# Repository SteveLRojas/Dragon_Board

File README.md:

# Dragon_Board
Custom FPGA board designed for TRS-80 and NES projects.

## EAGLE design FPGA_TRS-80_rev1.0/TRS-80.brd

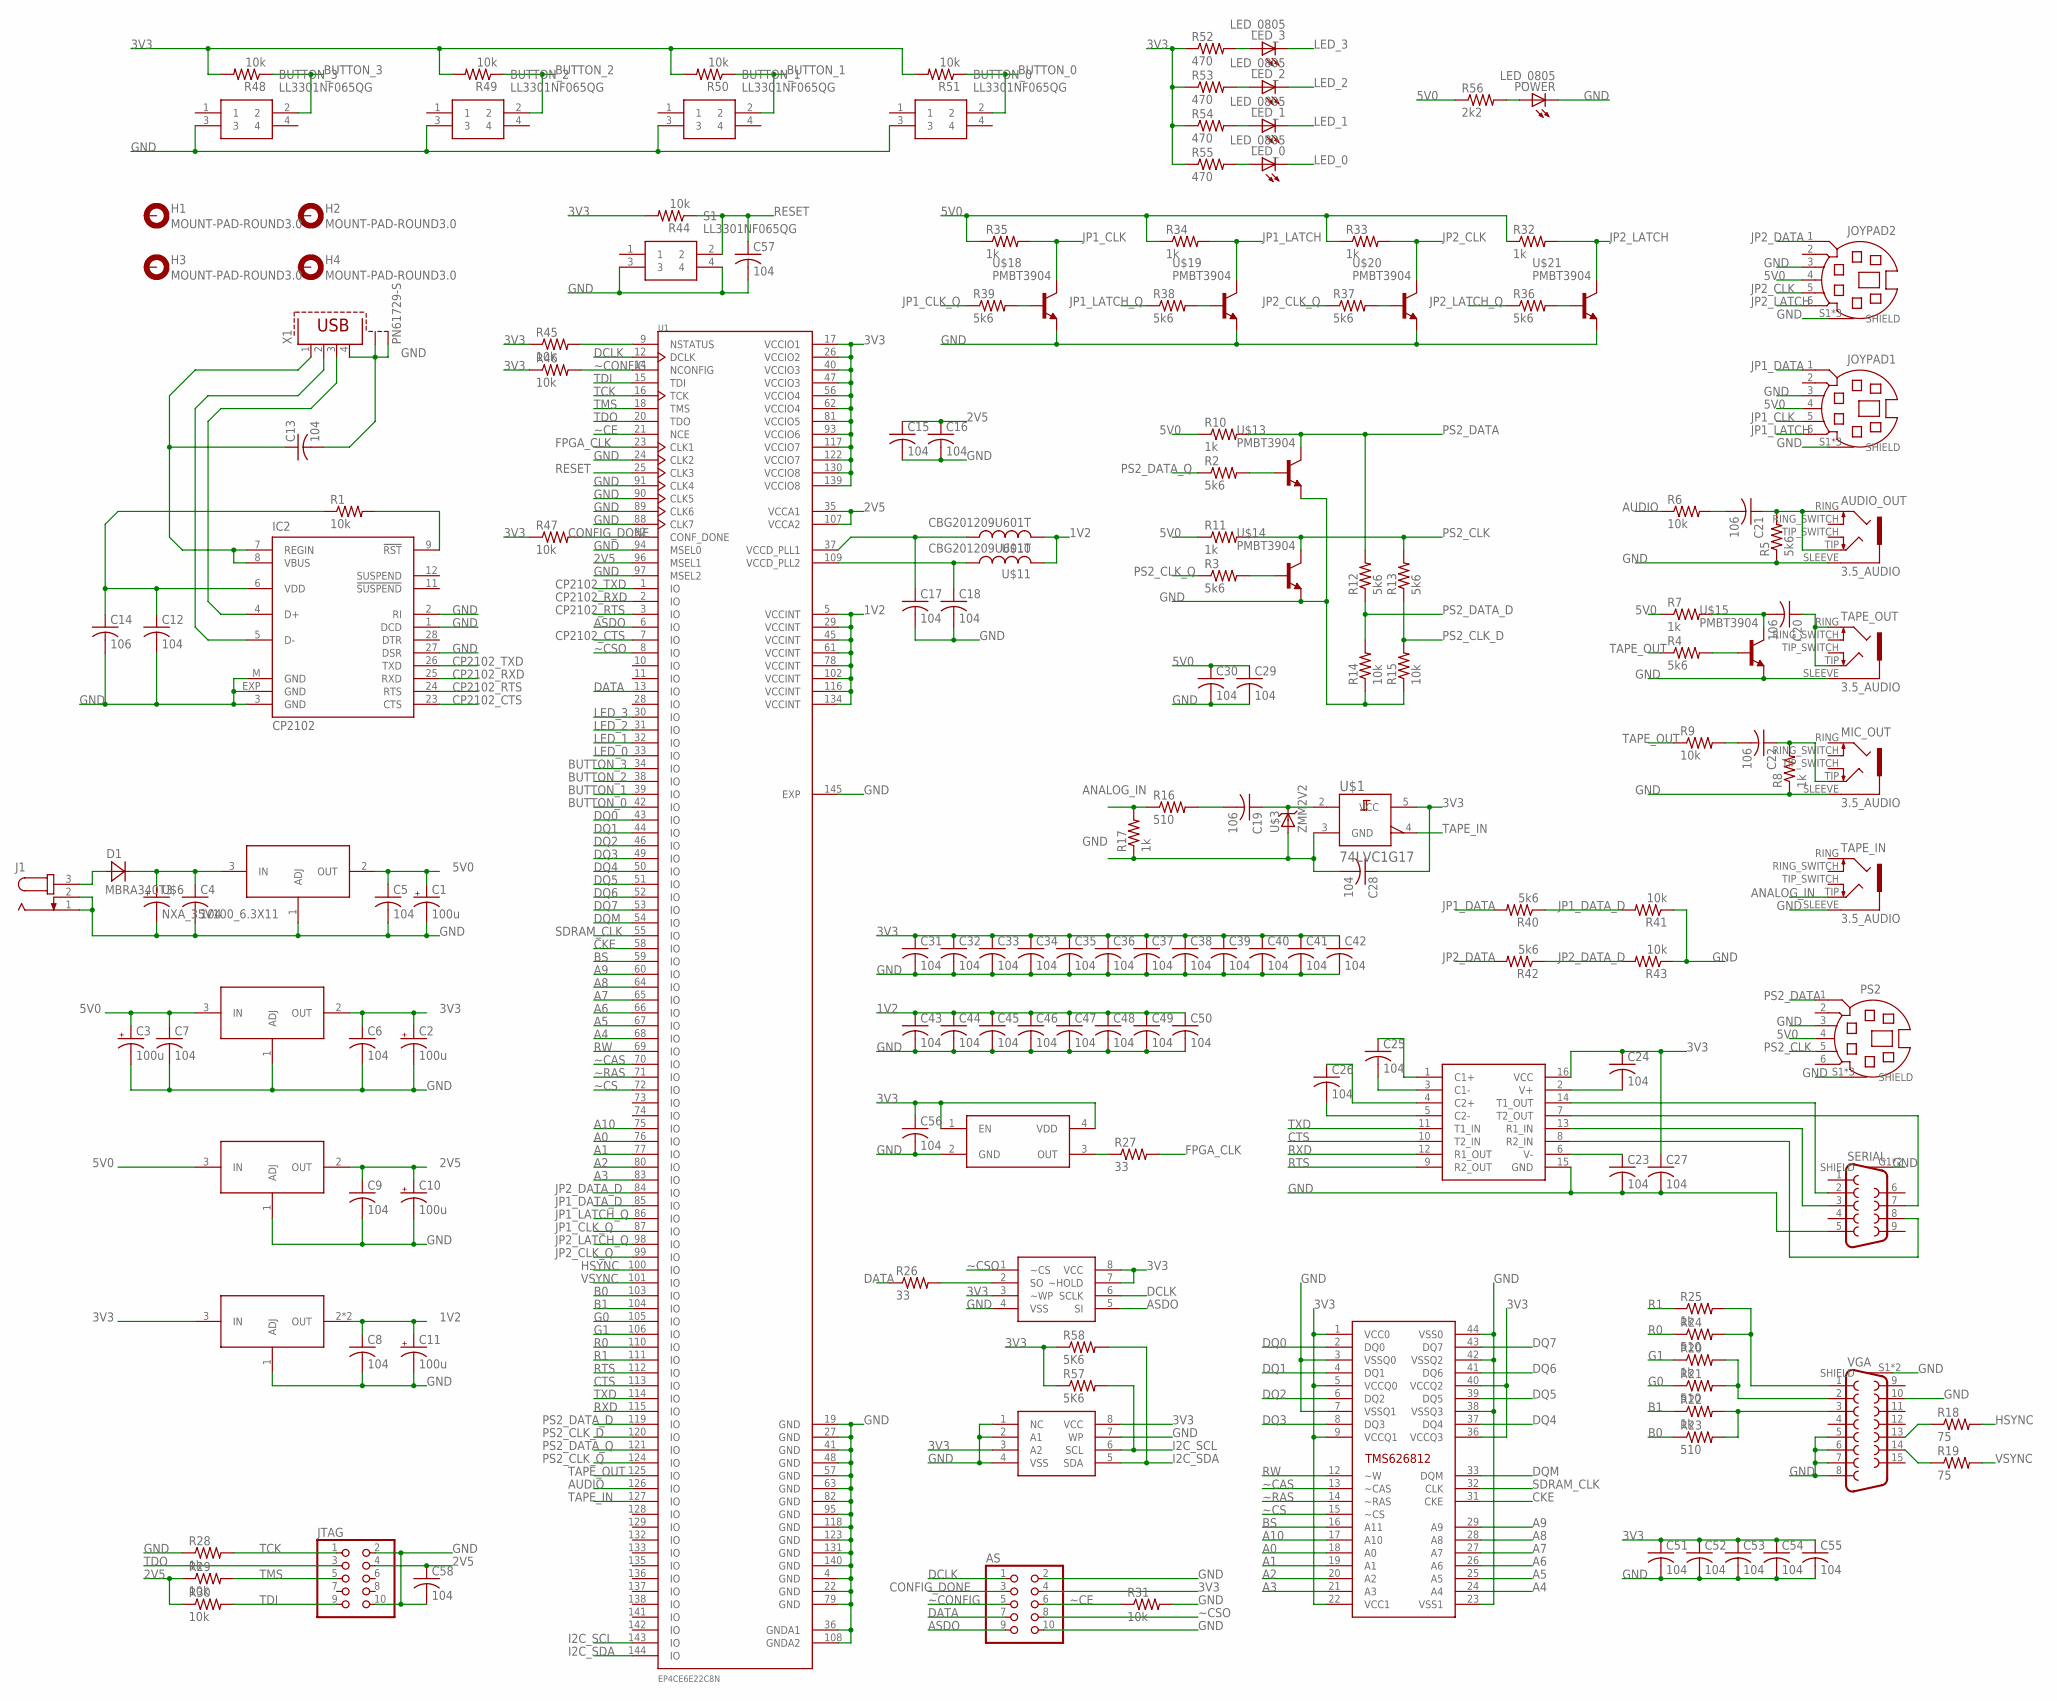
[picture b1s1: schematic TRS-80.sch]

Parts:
AS: PINHD-2X5; 2X05
AUDIO_OUT: 3.5_AUDIO
BUTTON_0, BUTTON_1, BUTTON_2, BUTTON_3: LL3301NF065QG
C1, C2, C3, C10, C11: 100u; UD-6,3X5,8_NICHICON
C4, C5, C6, C7, C8, C9, C12, C13, C15, C16, C17, C18, C23, C24, C25, C26, C27, C28, C29, C30, C31, C32, C33, C34, C35, C36, C37, C38, C39, C40, C41, C42, C43, C44, C45, C46, C47, C48, C49, C50, C51, C52, C53, C54, C55, C56, C57, C58: 104; C0805
C14, C19, C20, C21, C22: 106; C1206
D1: MBRA340T3; SMA
H1, H2, H3, H4: MOUNT-PAD-ROUND3.0; 3,0-PAD
IC2: CP2102; MLP28
J1: JACK-PLUG1; SPC4078
JOYPAD1, JOYPAD2: MD06SS; MDIN06SS
JTAG: PINHD-2X5; 2X05
LED_0, LED_1, LED_2, LED_3: LED_0805; CHIP-LED0805
MIC_OUT: 3.5_AUDIO
POWER: LED_0805; CHIP-LED0805
PS2: MD06SS; MDIN06SS
R1, R6, R9, R14, R15, R29, R30, R31, R41, R43, R44, R45, R46, R47, R48, R49, R50, R51: 10k; R0805
R2, R3, R4, R5, R12, R13, R36, R37, R38, R39, R40, R42: 5k6; R0805
R7, R8, R10, R11, R17, R20, R22, R25, R28, R32, R33, R34, R35: 1k; R0805
R16, R21, R23, R24: 510; R0805
R18, R19: 75; R0805
R26, R27: 33; R0805
R52, R53, R54, R55: 470; R0805
R56: 2k2; R0805
R57, R58: 5K6; R0805
S1: LL3301NF065QG
SERIAL: F09HP
TAPE_IN: 3.5_AUDIO
TAPE_OUT: 3.5_AUDIO
U1: EP4CE6E22C8N; QFP50P2200X2200X165-145N
U$1: 74LVC1G17; SOT353
U$2: TMS626812; TSOP44-II
U$3: ZMM2V2; SOD80C
U$4: SP232; SOP16
U$5: LM1086; D2PACK
U$6: NXA_35V100_6.3X11
U$7: LD1117D-3.3; TO252
U$8: KIA1117-2.5; SOT223
U$9: AZ1117H-1.2TRG1; SOT223
U$10, U$11: CBG201209U601T; C0805
U$12: OT705050MJBA4SL; ASV32000MHZET
U$13, U$14, U$15, U$18, U$19, U$20, U$21: PMBT3904; SOT23
U$16: BY25Q16BS; SO08
U$17: CAT24M01WI-GT3; SO08
VGA: F15HDH; HDF15H
X1: PN61729-S

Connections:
1V2: C8.1, C11.+, C43.1, C44.1, C45.1, C46.1, C47.1, C48.1, C49.1, C50.1, U1.5 (VCCINT), U1.29 (VCCINT), U1.45 (VCCINT), U1.61 (VCCINT), U1.78 (VCCINT), U1.102 (VCCINT), U1.116 (VCCINT), U1.134 (VCCINT), U$9.2 (OUT), U$9.4 (OUT), U$10.2, U$11.2
2V5: C9.1, C10.+, C15.1, C16.1, C58.1, JTAG.4, R29.1, R30.1, U1.35 (VCCA1), U1.96 (MSEL1), U1.107 (VCCA2), U$8.2 (OUT)
3V3: AS.4, C2.+, C6.1, C24.1, C27.1, C28.1, C31.1, C32.1, C33.1, C34.1, C35.1, C36.1, C37.1, C38.1, C39.1, C40.1, C41.1, C42.1, C51.1, C52.1, C53.1, C54.1, C55.1, C56.1, R44.2, R45.1, R46.1, R47.1, R48.2, R49.2, R50.2, R51.2, R52.1, R53.1, R54.1, R55.1, R57.1, R58.1, U1.17 (VCCIO1), U1.26 (VCCIO2), U1.40 (VCCIO3), U1.47 (VCCIO3), U1.56 (VCCIO4), U1.62 (VCCIO4), U1.81 (VCCIO5), U1.93 (VCCIO6), U1.117 (VCCIO7), U1.122 (VCCIO7), U1.130 (VCCIO8), U1.139 (VCCIO8), U$1.5 (VCC), U$2.1 (VCC0), U$2.5 (VCCQ0), U$2.9 (VCCQ1), U$2.22 (VCC1), U$2.36 (VCCQ3), U$2.40 (VCCQ2), U$4.16 (VCC), U$7.2 (OUT), U$9.3 (IN), U$12.1 (EN), U$12.4 (VDD), U$16.3 (~WP), U$16.7 (~HOLD), U$16.8 (VCC), U$17.3 (A2), U$17.8 (VCC)
5V0: C1.+, C3.+, C5.1, C7.1, C29.1, C30.1, JOYPAD1.4, JOYPAD2.4, PS2.4, R7.1, R10.1, R11.1, R32.1, R33.1, R34.1, R35.1, R56.1, U$5.2 (OUT), U$7.3 (IN), U$8.3 (IN)
A0: U1.76 (IO), U$2.18 (A0)
A1: U1.77 (IO), U$2.19 (A1)
A2: U1.80 (IO), U$2.20 (A2)
A3: U1.83 (IO), U$2.21 (A3)
A4: U1.68 (IO), U$2.24 (A4)
A5: U1.67 (IO), U$2.25 (A5)
A6: U1.66 (IO), U$2.26 (A6)
A7: U1.65 (IO), U$2.27 (A7)
A8: U1.64 (IO), U$2.28 (A8)
A9: U1.60 (IO), U$2.29 (A9)
A10: U1.75 (IO), U$2.17 (A10)
ANALOG_IN: R16.1, R17.2, TAPE_IN.TIP
ASDO: AS.9, U1.6 (IO), U$16.5 (SI)
AUDIO: R6.1, U1.126 (IO)
B0: R23.1, U1.103 (IO)
B1: R22.1, U1.104 (IO)
BS: U1.59 (IO), U$2.16 (A11)
BUTTON_0: BUTTON_0.2, R51.1, U1.42 (IO)
BUTTON_1: BUTTON_1.2, R50.1, U1.39 (IO)
BUTTON_2: BUTTON_2.2, R49.1, U1.38 (IO)
BUTTON_3: BUTTON_3.2, R48.1, U1.34 (IO)
CKE: U1.58 (IO), U$2.31 (CKE)
CONFIG_DONE: AS.3, R47.2, U1.92 (CONF_DONE)
CP2102_CTS: IC2.23 (CTS), U1.7 (IO)
CP2102_RTS: IC2.24 (RTS), U1.3 (IO)
CP2102_RXD: IC2.25 (RXD), U1.2 (IO)
CP2102_TXD: IC2.26 (TXD), U1.1 (IO)
CTS: U1.113 (IO), U$4.10 (T2_IN)
DATA: AS.7, R26.1, U1.13 (IO)
DCLK: AS.1, U1.12 (DCLK), U$16.6 (SCLK)
DQ0: U1.43 (IO), U$2.2 (DQ0)
DQ1: U1.44 (IO), U$2.4 (DQ1)
DQ2: U1.46 (IO), U$2.6 (DQ2)
DQ3: U1.49 (IO), U$2.8 (DQ3)
DQ4: U1.50 (IO), U$2.37 (DQ4)
DQ5: U1.51 (IO), U$2.39 (DQ5)
DQ6: U1.52 (IO), U$2.41 (DQ6)
DQ7: U1.53 (IO), U$2.43 (DQ7)
DQM: U1.54 (IO), U$2.33 (DQM)
FPGA_CLK: R27.2, U1.23 (CLK1)
G0: R21.1, U1.105 (IO)
G1: R20.1, U1.106 (IO)
GND: AS.2, AS.10, AUDIO_OUT.SLEEVE, BUTTON_0.3, BUTTON_1.3, BUTTON_2.3, BUTTON_3.3, C1.-, C2.-, C3.-, C4.2, C5.2, C6.2, C7.2, C8.2, C9.2, C10.-, C11.-, C12.2, C13.2, C14.2, C15.2, C16.2, C17.2, C18.2, C23.2, C27.2, C28.2, C29.2, C30.2, C31.2, C32.2, C33.2, C34.2, C35.2, C36.2, C37.2, C38.2, C39.2, C40.2, C41.2, C42.2, C43.2, C44.2, C45.2, C46.2, C47.2, C48.2, C49.2, C50.2, C51.2, C52.2, C53.2, C54.2, C55.2, C56.2, C57.2, C58.2, IC2.1 (DCD), IC2.2 (RI), IC2.3 (GND), IC2.27 (DSR), IC2.EXP (GND), IC2.M (GND), J1.1, J1.2, JOYPAD1.3, JOYPAD1.S1 (SHIELD), JOYPAD1.S2 (SHIELD), JOYPAD1.S3 (SHIELD), JOYPAD2.3, JOYPAD2.S1 (SHIELD), JOYPAD2.S2 (SHIELD), JOYPAD2.S3 (SHIELD), JTAG.2, JTAG.10, MIC_OUT.SLEEVE, POWER.C, PS2.3, PS2.S1 (SHIELD), PS2.S2 (SHIELD), PS2.S3 (SHIELD), R5.1, R8.1, R14.1, R15.1, R17.1, R28.1, R31.2, R41.1, R43.1, S1.3, S1.4, SERIAL.5, SERIAL.G1 (SHIELD), SERIAL.G2 (SHIELD), TAPE_IN.SLEEVE, TAPE_OUT.SLEEVE, U1.4 (GND), U1.19 (GND), U1.22 (GND), U1.24 (CLK2), U1.27 (GND), U1.36 (GNDA1), U1.41 (GND), U1.48 (GND), U1.57 (GND), U1.63 (GND), U1.79 (GND), U1.82 (GND), U1.88 (CLK7), U1.89 (CLK6), U1.90 (CLK5), U1.91 (CLK4), U1.94 (MSEL0), U1.95 (GND), U1.97 (MSEL2), U1.108 (GNDA2), U1.118 (GND), U1.123 (GND), U1.131 (GND), U1.140 (GND), U1.145 (EXP), U$1.3 (GND), U$2.3 (VSSQ0), U$2.7 (VSSQ1), U$2.23 (VSS1), U$2.38 (VSSQ3), U$2.42 (VSSQ2), U$2.44 (VSS0), U$3.A, U$4.15 (GND), U$5.1 (ADJ), U$6.P$1 (-), U$7.1 (ADJ), U$8.1 (ADJ), U$9.1 (ADJ), U$12.2 (GND), U$13.2 (E), U$14.2 (E), U$15.2 (E), U$16.4 (VSS), U$17.1 (NC), U$17.2 (A1), U$17.4 (VSS), U$17.7 (WP), U$18.2 (E), U$19.2 (E), U$20.2 (E), U$21.2 (E), VGA.5, VGA.6, VGA.7, VGA.8, VGA.10, VGA.S1 (SHIELD), VGA.S2 (SHIELD), X1.4, X1.S1, X1.S2
HSYNC: R18.2, U1.100 (IO)
I2C_SCL: R57.2, U1.143 (IO), U$17.6 (SCL)
I2C_SDA: R58.2, U1.144 (IO), U$17.5 (SDA)
JP1_CLK: JOYPAD1.5, R35.2, U$18.3 (C)
JP1_CLK_Q: R39.1, U1.87 (IO)
JP1_DATA: JOYPAD1.1, R40.2
JP1_DATA_D: R40.1, R41.2, U1.85 (IO)
JP1_LATCH: JOYPAD1.6, R34.2, U$19.3 (C)
JP1_LATCH_Q: R38.1, U1.86 (IO)
JP2_CLK: JOYPAD2.5, R33.2, U$20.3 (C)
JP2_CLK_Q: R37.1, U1.99 (IO)
JP2_DATA: JOYPAD2.1, R42.2
JP2_DATA_D: R42.1, R43.2, U1.84 (IO)
JP2_LATCH: JOYPAD2.6, R32.2, U$21.3 (C)
JP2_LATCH_Q: R36.1, U1.98 (IO)
LED_0: LED_0.C, U1.33 (IO)
LED_1: LED_1.C, U1.32 (IO)
LED_2: LED_2.C, U1.31 (IO)
LED_3: LED_3.C, U1.30 (IO)
unnamed: C17.1, U1.37 (VCCD_PLL1), U$10.1
unnamed: IC2.5 (D-), X1.2
unnamed: IC2.4 (D+), X1.3
unnamed: IC2.9 (!RST), R1.2
unnamed: LED_3.A, R52.2
unnamed: C18.1, U1.109 (VCCD_PLL2), U$11.1
unnamed: C12.1, C14.1, IC2.6 (VDD), R1.1
unnamed: R2.2, U$13.1 (B)
unnamed: R3.2, U$14.1 (B)
unnamed: R4.2, U$15.1 (B)
unnamed: C22.1, MIC_OUT.TIP, R8.2
unnamed: C20.2, R7.2, U$15.3 (C)
unnamed: C19.1, U$1.2 (A), U$3.C
unnamed: AUDIO_OUT.RING, AUDIO_OUT.TIP, C21.1, R5.2
unnamed: C19.2, R16.2
unnamed: C20.1, TAPE_OUT.RING, TAPE_OUT.TIP
unnamed: C21.2, R6.2
unnamed: R18.1, VGA.13
unnamed: R19.1, VGA.14
unnamed: R22.2, R23.2, VGA.3
unnamed: R20.2, R21.2, VGA.2
unnamed: R24.2, R25.2, VGA.1
unnamed: C22.2, R9.2
unnamed: SERIAL.2, U$4.14 (T1_OUT)
unnamed: SERIAL.3, U$4.13 (R1_IN)
unnamed: SERIAL.8, U$4.8 (R2_IN)
unnamed: SERIAL.7, U$4.7 (T2_OUT)
unnamed: C23.1, U$4.6 (V-)
unnamed: C24.2, U$4.2 (V+)
unnamed: C25.2, U$4.3 (C1-)
unnamed: C25.1, U$4.1 (C1+)
unnamed: C26.1, U$4.4 (C2+)
unnamed: C26.2, U$4.5 (C2-)
unnamed: R26.2, U$16.2 (SO)
unnamed: R27.1, U$12.3 (OUT)
unnamed: LED_2.A, R53.2
unnamed: LED_1.A, R54.2
unnamed: LED_0.A, R55.2
unnamed: R39.2, U$18.1 (B)
unnamed: R38.2, U$19.1 (B)
unnamed: R37.2, U$20.1 (B)
unnamed: R36.2, U$21.1 (B)
unnamed: POWER.A, R56.2
unnamed: R45.2, U1.9 (NSTATUS)
PS2_CLK: PS2.5, R11.2, R13.2, U$14.3 (C)
PS2_CLK_D: R13.1, R15.2, U1.120 (IO)
PS2_CLK_Q: R3.1, U1.124 (IO)
PS2_DATA: PS2.1, R10.2, R12.2, U$13.3 (C)
PS2_DATA_D: R12.1, R14.2, U1.119 (IO)
PS2_DATA_Q: R2.1, U1.121 (IO)
R0: R24.1, U1.110 (IO)
R1: R25.1, U1.111 (IO)
RESET: C57.1, R44.1, S1.2, U1.25 (CLK3)
RTS: U1.112 (IO), U$4.9 (R2_OUT)
RW: U1.69 (IO), U$2.12 (~W)
RXD: U1.115 (IO), U$4.12 (R1_OUT)
SDRAM_CLK: U1.55 (IO), U$2.32 (CLK)
TAPE_IN: U1.127 (IO), U$1.4 (Y)
TAPE_OUT: R4.1, R9.1, U1.125 (IO)
TCK: JTAG.1, R28.2, U1.16 (TCK)
TDI: JTAG.9, R30.2, U1.15 (TDI)
TDO: JTAG.3, U1.20 (TDO)
TMS: JTAG.5, R29.2, U1.18 (TMS)
TXD: U1.114 (IO), U$4.11 (T1_IN)
VBUS: C13.1, IC2.7 (REGIN), IC2.8 (VBUS), X1.1
VHIGH: C4.1, D1.C, U$5.3 (IN), U$6.P$2 (+)
VIN: D1.A, J1.3
VSYNC: R19.2, U1.101 (IO)
~CAS: U1.70 (IO), U$2.13 (~CAS)
~CE: AS.6, R31.1, U1.21 (NCE)
~CONFIG: AS.5, R46.2, U1.14 (NCONFIG)
~CS: U1.72 (IO), U$2.15 (~CS)
~CSO: AS.8, U1.8 (IO), U$16.1 (~CS)
~RAS: U1.71 (IO), U$2.14 (~RAS)

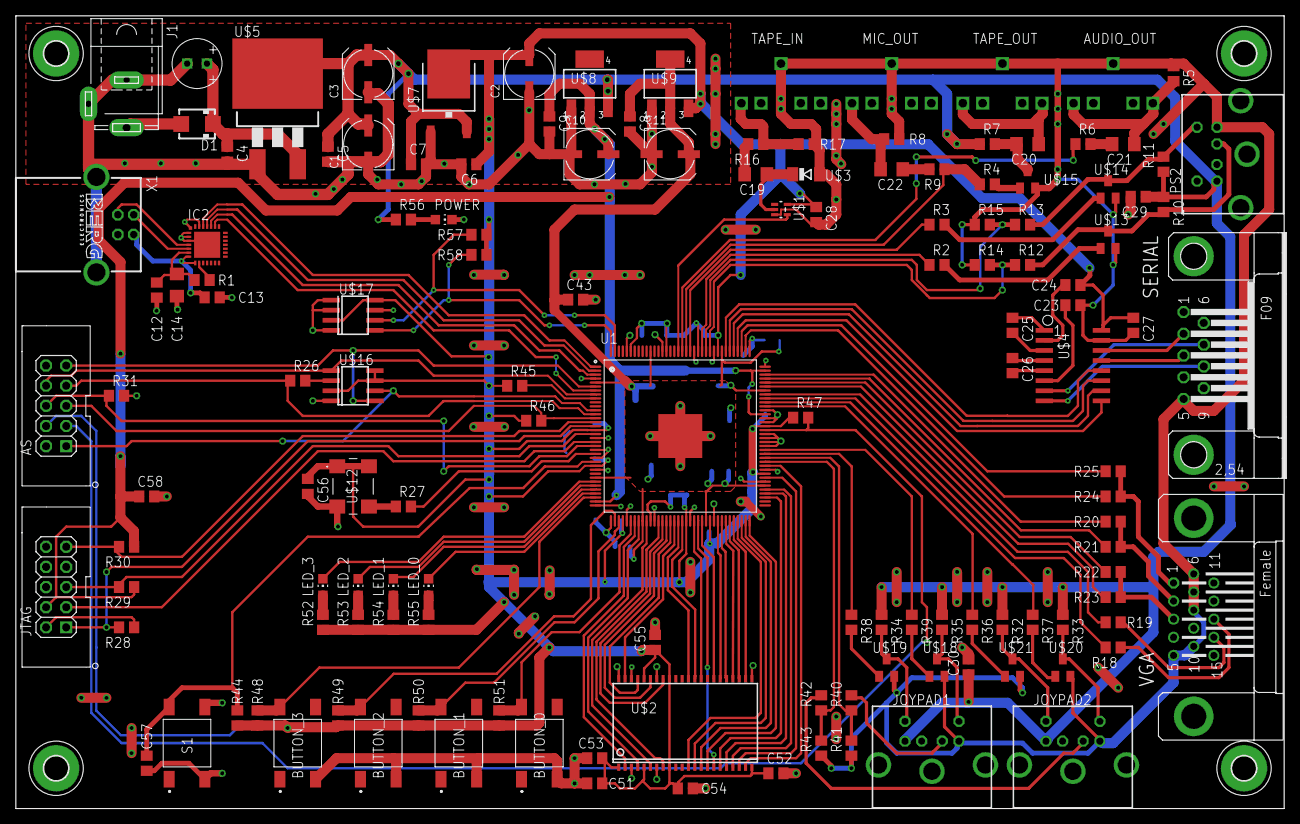
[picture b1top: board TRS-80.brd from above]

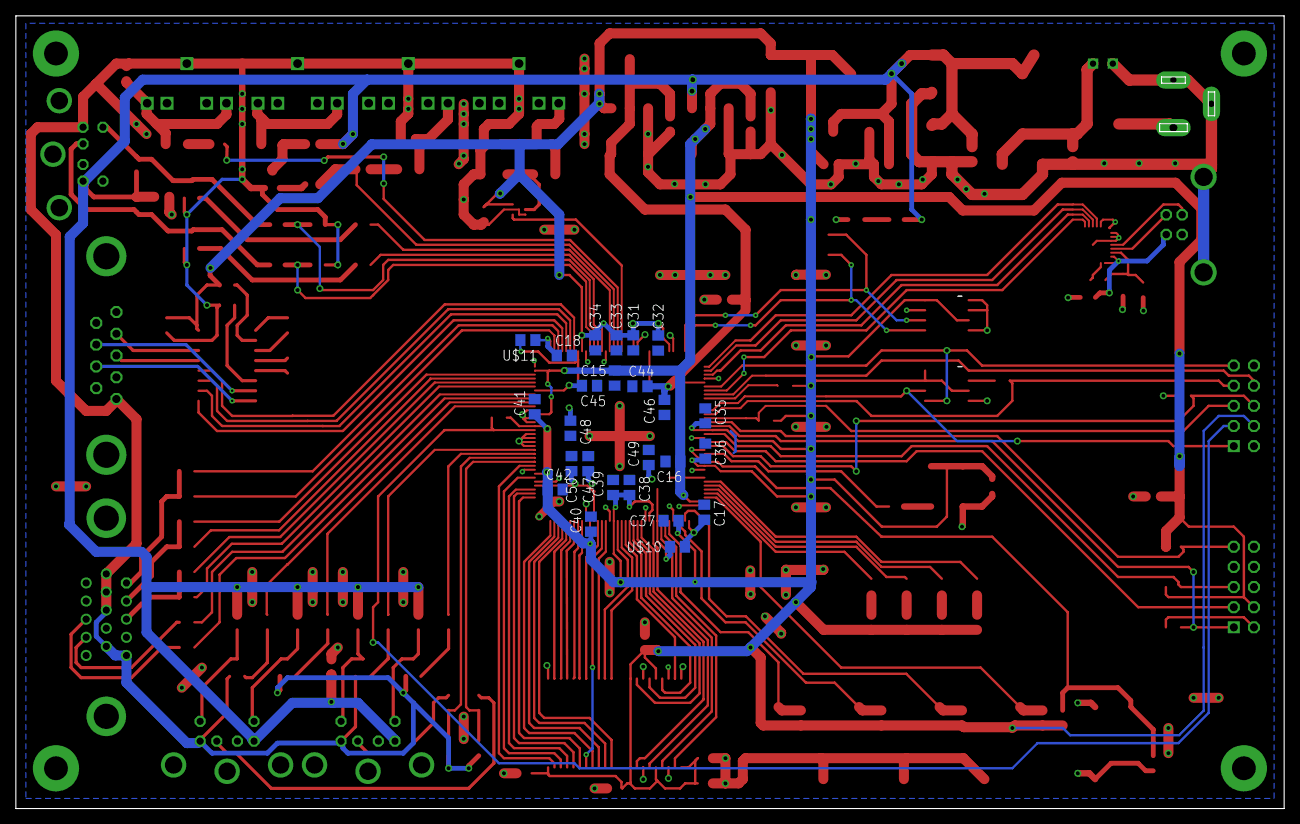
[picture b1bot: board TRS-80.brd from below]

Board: 2 copper layers, 160.0 x 100.0 mm, 167 parts (25 on the bottom side), 140 nets.

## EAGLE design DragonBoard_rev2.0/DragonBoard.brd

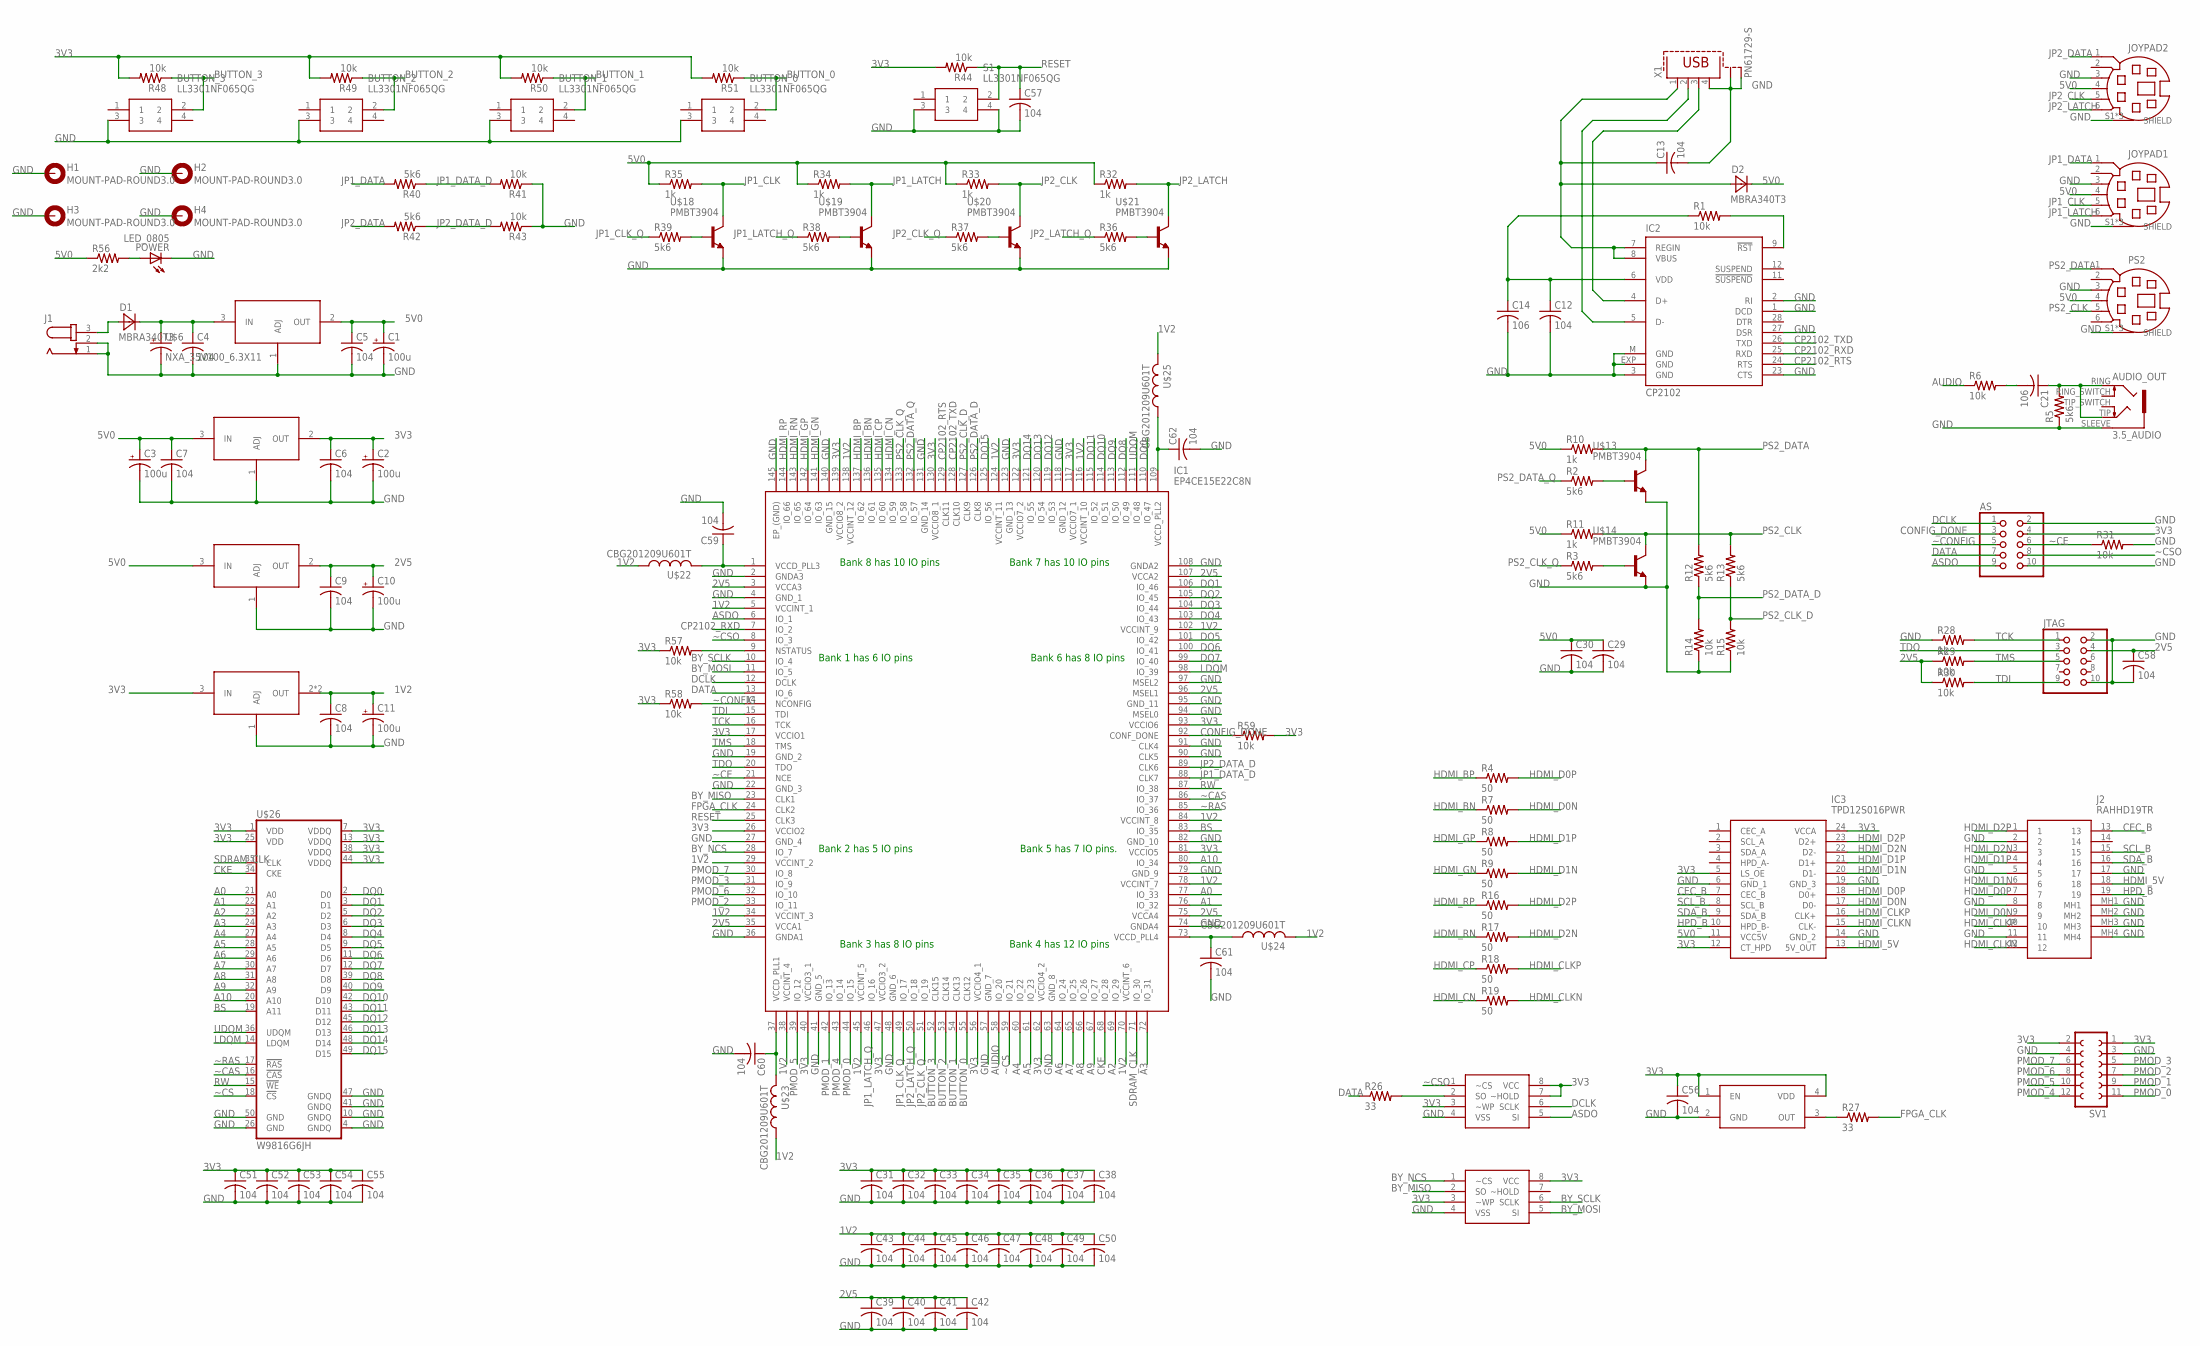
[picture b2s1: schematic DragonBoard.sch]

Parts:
AS: PINHD-2X5; 2X05
AUDIO_OUT: 3.5_AUDIO
BUTTON_0, BUTTON_1, BUTTON_2, BUTTON_3: LL3301NF065QG
C1, C2, C3, C10, C11: 100u; UD-6,3X5,8_NICHICON
C4, C5, C6, C7, C8, C9, C12, C13, C29, C30, C31, C32, C33, C34, C35, C36, C37, C38, C39, C40, C41, C42, C43, C44, C45, C46, C47, C48, C49, C50, C51, C52, C53, C54, C55, C56, C57, C58, C59, C60, C61, C62: 104; C0805
C14, C21: 106; C1206
D1, D2: MBRA340T3; SMA
H1, H2, H3, H4: MOUNT-PAD-ROUND3.0; 3,0-PAD
IC1: EP4CE15E22C8N; QFP50P2200X2200X165-145N
IC2: CP2102; MLP28
IC3: TPD12S016PWR; SOP65P640X120-24N
J1: JACK-PLUG1; SPC4078
J2: RAHHD19TR
JOYPAD1, JOYPAD2: MD06SS; MDIN06SS
JTAG: PINHD-2X5; 2X05
POWER: LED_0805; CHIP-LED0805
PS2: MD06SS; MDIN06SS
R1, R6, R14, R15, R29, R30, R31, R41, R43, R44, R48, R49, R50, R51, R57, R58, R59: 10k; R0805
R2, R3, R5, R12, R13, R36, R37, R38, R39, R40, R42: 5k6; R0805
R4, R7, R8, R9, R16, R17, R18, R19: 50; R0805
R10, R11, R28, R32, R33, R34, R35: 1k; R0805
R26, R27: 33; R0805
R56: 2k2; R0805
S1: LL3301NF065QG
SV1: FE06-2W
U$1, U$16: BY25Q16BS; SO08
U$5: LM1086; D2PACK
U$6: NXA_35V100_6.3X11
U$7: LD1117D-3.3; TO252
U$8: KIA1117-2.5; SOT223
U$9: AZ1117H-1.2TRG1; SOT223
U$12: OT705050MJBA4SL; ASV32000MHZET
U$13, U$14, U$18, U$19, U$20, U$21: PMBT3904; SOT23
U$22, U$23, U$24, U$25: CBG201209U601T; C0805
U$26: W9816G6JH; TSOP50-II
X1: PN61729-S

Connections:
1V2: C8.1, C11.+, C43.1, C44.1, C45.1, C46.1, C47.1, C48.1, C49.1, C50.1, IC1.5 (VCCINT_1), IC1.29 (VCCINT_2), IC1.34 (VCCINT_3), IC1.38 (VCCINT_4), IC1.45 (VCCINT_5), IC1.70 (VCCINT_6), IC1.78 (VCCINT_7), IC1.84 (VCCINT_8), IC1.102 (VCCINT_9), IC1.116 (VCCINT_10), IC1.124 (VCCINT_11), IC1.138 (VCCINT_12), U$9.2 (OUT), U$9.4 (OUT), U$22.1, U$23.1, U$24.2, U$25.2
2V5: C9.1, C10.+, C39.1, C40.1, C41.1, C42.1, C58.1, IC1.3 (VCCA3), IC1.35 (VCCA1), IC1.75 (VCCA4), IC1.96 (MSEL1), IC1.107 (VCCA2), JTAG.4, R29.1, R30.1, U$8.2 (OUT)
3V3: AS.4, C2.+, C6.1, C31.1, C32.1, C33.1, C34.1, C35.1, C36.1, C37.1, C38.1, C51.1, C52.1, C53.1, C54.1, C55.1, C56.1, IC1.17 (VCCIO1), IC1.26 (VCCIO2), IC1.40 (VCCIO3_1), IC1.47 (VCCIO3_2), IC1.56 (VCCIO4_1), IC1.62 (VCCIO4_2), IC1.81 (VCCIO5), IC1.93 (VCCIO6), IC1.117 (VCCIO7_1), IC1.122 (VCCIO7_2), IC1.130 (VCCIO8_1), IC1.139 (VCCIO8_2), IC3.5 (LS_OE), IC3.12 (CT_HPD), IC3.24 (VCCA), R44.2, R48.2, R49.2, R50.2, R51.2, R57.1, R58.1, R59.2, SV1.1, SV1.2, U$1.3 (~WP), U$1.8 (VCC), U$7.2 (OUT), U$9.3 (IN), U$12.1 (EN), U$12.4 (VDD), U$16.3 (~WP), U$16.7 (~HOLD), U$16.8 (VCC), U$26.1 (VDD), U$26.7 (VDDQ), U$26.13 (VDDQ), U$26.25 (VDD), U$26.38 (VDDQ), U$26.44 (VDDQ)
5V0: C1.+, C3.+, C5.1, C7.1, C29.1, C30.1, D2.C, IC3.11 (VCC5V), JOYPAD1.4, JOYPAD2.4, PS2.4, R10.1, R11.1, R32.1, R33.1, R34.1, R35.1, R56.1, U$5.2 (OUT), U$7.3 (IN), U$8.3 (IN)
A0: IC1.77 (IO_33), U$26.21 (A0)
A1: IC1.76 (IO_32), U$26.22 (A1)
A2: IC1.69 (IO_29), U$26.23 (A2)
A3: IC1.72 (IO_31), U$26.24 (A3)
A4: IC1.60 (IO_22), U$26.27 (A4)
A5: IC1.61 (IO_23), U$26.28 (A5)
A6: IC1.64 (IO_24), U$26.29 (A6)
A7: IC1.65 (IO_25), U$26.30 (A7)
A8: IC1.66 (IO_26), U$26.31 (A8)
A9: IC1.67 (IO_27), U$26.32 (A9)
A10: IC1.80 (IO_34), U$26.20 (A10)
ASDO: AS.9, IC1.6 (IO_1), U$16.5 (SI)
AUDIO: IC1.58 (IO_20), R6.1
BS: IC1.83 (IO_35), U$26.19 (A11)
BUTTON_0: BUTTON_0.2, IC1.55 (CLK12), R51.1
BUTTON_1: BUTTON_1.2, IC1.54 (CLK13), R50.1
BUTTON_2: BUTTON_2.2, IC1.53 (CLK14), R49.1
BUTTON_3: BUTTON_3.2, IC1.52 (CLK15), R48.1
BY_MISO: IC1.23 (CLK1), U$1.2 (SO)
BY_MOSI: IC1.11 (IO_5), U$1.5 (SI)
BY_NCS: IC1.28 (IO_7), U$1.1 (~CS)
BY_SCLK: IC1.10 (IO_4), U$1.6 (SCLK)
CEC_B: IC3.7 (CEC_B), J2.13
CKE: IC1.68 (IO_28), U$26.34 (CKE)
CONFIG_DONE: AS.3, IC1.92 (CONF_DONE), R59.1
CP2102_RTS: IC1.129 (CLK11), IC2.24 (RTS)
CP2102_RXD: IC1.7 (IO_2), IC2.25 (RXD)
CP2102_TXD: IC1.128 (CLK10), IC2.26 (TXD)
DATA: AS.7, IC1.13 (IO_6), R26.1
DCLK: AS.1, IC1.12 (DCLK), U$16.6 (SCLK)
DQ0: IC1.110 (IO_47), U$26.2 (D0)
DQ1: IC1.106 (IO_46), U$26.3 (D1)
DQ2: IC1.105 (IO_45), U$26.5 (D2)
DQ3: IC1.104 (IO_44), U$26.6 (D3)
DQ4: IC1.103 (IO_43), U$26.8 (D4)
DQ5: IC1.101 (IO_42), U$26.9 (D5)
DQ6: IC1.100 (IO_41), U$26.11 (D6)
DQ7: IC1.99 (IO_40), U$26.12 (D7)
DQ8: IC1.112 (IO_49), U$26.39 (D8)
DQ9: IC1.113 (IO_50), U$26.40 (D9)
DQ10: IC1.114 (IO_51), U$26.42 (D10)
DQ11: IC1.115 (IO_52), U$26.43 (D11)
DQ12: IC1.119 (IO_53), U$26.45 (D12)
DQ13: IC1.120 (IO_54), U$26.46 (D13)
DQ14: IC1.121 (IO_55), U$26.48 (D14)
DQ15: IC1.125 (IO_56), U$26.49 (D15)
FPGA_CLK: IC1.24 (CLK2), R27.2
GND: AS.2, AS.10, AUDIO_OUT.SLEEVE, BUTTON_0.3, BUTTON_1.3, BUTTON_2.3, BUTTON_3.3, C1.-, C2.-, C3.-, C4.2, C5.2, C6.2, C7.2, C8.2, C9.2, C10.-, C11.-, C12.2, C13.2, C14.2, C29.2, C30.2, C31.2, C32.2, C33.2, C34.2, C35.2, C36.2, C37.2, C38.2, C39.2, C40.2, C41.2, C42.2, C43.2, C44.2, C45.2, C46.2, C47.2, C48.2, C49.2, C50.2, C51.2, C52.2, C53.2, C54.2, C55.2, C56.2, C57.2, C58.2, C59.2, C60.2, C61.2, C62.2, H1.B3,0, H2.B3,0, H3.B3,0, H4.B3,0, IC1.2 (GNDA3), IC1.4 (GND_1), IC1.19 (GND_2), IC1.22 (GND_3), IC1.27 (GND_4), IC1.36 (GNDA1), IC1.41 (GND_5), IC1.48 (GND_6), IC1.57 (GND_7), IC1.63 (GND_8), IC1.74 (GNDA4), IC1.79 (GND_9), IC1.82 (GND_10), IC1.90 (CLK5), IC1.91 (CLK4), IC1.94 (MSEL0), IC1.95 (GND_11), IC1.97 (MSEL2), IC1.108 (GNDA2), IC1.118 (GND_12), IC1.123 (GND_13), IC1.131 (GND_14), IC1.140 (GND_15), IC1.145 (EP_(GND)), IC2.1 (DCD), IC2.2 (RI), IC2.3 (GND), IC2.23 (CTS), IC2.27 (DSR), IC2.EXP (GND), IC2.M (GND), IC3.6 (GND_1), IC3.14 (GND_2), IC3.19 (GND_3), J1.1, J1.2, J2.2, J2.5, J2.8, J2.11, J2.17, J2.MH1, J2.MH2, J2.MH3, J2.MH4, JOYPAD1.3, JOYPAD1.S1 (SHIELD), JOYPAD1.S2 (SHIELD), JOYPAD1.S3 (SHIELD), JOYPAD2.3, JOYPAD2.S1 (SHIELD), JOYPAD2.S2 (SHIELD), JOYPAD2.S3 (SHIELD), JTAG.2, JTAG.10, POWER.C, PS2.3, PS2.S1 (SHIELD), PS2.S2 (SHIELD), PS2.S3 (SHIELD), R5.1, R14.1, R15.1, R28.1, R31.2, R41.1, R43.1, S1.3, S1.4, SV1.3, SV1.4, U$1.4 (VSS), U$5.1 (ADJ), U$6.P$1 (-), U$7.1 (ADJ), U$8.1 (ADJ), U$9.1 (ADJ), U$12.2 (GND), U$13.2 (E), U$14.2 (E), U$16.4 (VSS), U$18.2 (E), U$19.2 (E), U$20.2 (E), U$21.2 (E), U$26.4 (GNDQ), U$26.10 (GNDQ), U$26.26 (GND), U$26.41 (GNDQ), U$26.47 (GNDQ), U$26.50 (GND), X1.4, X1.S1, X1.S2
HDMI_5V: IC3.13 (5V_OUT), J2.18
HDMI_BN: IC1.136 (IO_61), R7.1
HDMI_BP: IC1.137 (IO_62), R4.1
HDMI_CLKN: IC3.15 (CLK-), J2.12, R19.2
HDMI_CLKP: IC3.16 (CLK+), J2.10, R18.2
HDMI_CN: IC1.134 (IO_59), R19.1
HDMI_CP: IC1.135 (IO_60), R18.1
HDMI_D0N: IC3.17 (D0-), J2.9, R7.2
HDMI_D0P: IC3.18 (D0+), J2.7, R4.2
HDMI_D1N: IC3.20 (D1-), J2.6, R9.2
HDMI_D1P: IC3.21 (D1+), J2.4, R8.2
HDMI_D2N: IC3.22 (D2-), J2.3, R17.2
HDMI_D2P: IC3.23 (D2+), J2.1, R16.2
HDMI_GN: IC1.141 (IO_63), R9.1
HDMI_GP: IC1.142 (IO_64), R8.1
HDMI_RN: IC1.143 (IO_65), R17.1
HDMI_RP: IC1.144 (IO_66), R16.1
HPD_B: IC3.10 (HPD_B-), J2.19
JP1_CLK: JOYPAD1.5, R35.2, U$18.3 (C)
JP1_CLK_Q: IC1.49 (IO_17), R39.1
JP1_DATA: JOYPAD1.1, R40.2
JP1_DATA_D: IC1.88 (CLK7), R40.1, R41.2
JP1_LATCH: JOYPAD1.6, R34.2, U$19.3 (C)
JP1_LATCH_Q: IC1.46 (IO_16), R38.1
JP2_CLK: JOYPAD2.5, R33.2, U$20.3 (C)
JP2_CLK_Q: IC1.51 (IO_19), R37.1
JP2_DATA: JOYPAD2.1, R42.2
JP2_DATA_D: IC1.89 (CLK6), R42.1, R43.2
JP2_LATCH: JOYPAD2.6, R32.2, U$21.3 (C)
JP2_LATCH_Q: IC1.50 (IO_18), R36.1
LDQM: IC1.98 (IO_39), U$26.14 (LDQM)
unnamed: IC2.9 (!RST), R1.2
unnamed: C12.1, C14.1, IC2.6 (VDD), R1.1
unnamed: R2.2, U$13.1 (B)
unnamed: R3.2, U$14.1 (B)
unnamed: AUDIO_OUT.RING, AUDIO_OUT.TIP, C21.1, R5.2
unnamed: C21.2, R6.2
unnamed: C60.1, IC1.37 (VCCD_PLL1), U$23.2
unnamed: C59.1, IC1.1 (VCCD_PLL3), U$22.2
unnamed: C62.1, IC1.109 (VCCD_PLL2), U$25.1
unnamed: R26.2, U$16.2 (SO)
unnamed: R27.1, U$12.3 (OUT)
unnamed: R39.2, U$18.1 (B)
unnamed: R38.2, U$19.1 (B)
unnamed: R37.2, U$20.1 (B)
unnamed: R36.2, U$21.1 (B)
unnamed: POWER.A, R56.2
unnamed: C61.1, IC1.73 (VCCD_PLL4), U$24.1
unnamed: IC1.9 (NSTATUS), R57.2
PMOD_0: IC1.44 (IO_15), SV1.11
PMOD_1: IC1.42 (IO_13), SV1.9
PMOD_2: IC1.33 (IO_11), SV1.7
PMOD_3: IC1.31 (IO_9), SV1.5
PMOD_4: IC1.43 (IO_14), SV1.12
PMOD_5: IC1.39 (IO_12), SV1.10
PMOD_6: IC1.32 (IO_10), SV1.8
PMOD_7: IC1.30 (IO_8), SV1.6
PS2_CLK: PS2.5, R11.2, R13.2, U$14.3 (C)
PS2_CLK_D: IC1.127 (CLK9), R13.1, R15.2
PS2_CLK_Q: IC1.133 (IO_58), R3.1
PS2_DATA: PS2.1, R10.2, R12.2, U$13.3 (C)
PS2_DATA_D: IC1.126 (CLK8), R12.1, R14.2
PS2_DATA_Q: IC1.132 (IO_57), R2.1
RESET: C57.1, IC1.25 (CLK3), R44.1, S1.2
RW: IC1.87 (IO_38), U$26.15 (!WE)
SCL_B: IC3.8 (SCL_B), J2.15
SDA_B: IC3.9 (SDA_B), J2.16
SDRAM_CLK: IC1.71 (IO_30), U$26.35 (CLK)
TCK: IC1.16 (TCK), JTAG.1, R28.2
TDI: IC1.15 (TDI), JTAG.9, R30.2
TDO: IC1.20 (TDO), JTAG.3
TMS: IC1.18 (TMS), JTAG.5, R29.2
UDQM: IC1.111 (IO_48), U$26.36 (UDQM)
USB_DN: IC2.5 (D-), X1.2
USB_DP: IC2.4 (D+), X1.3
VBUS: C13.1, D2.A, IC2.7 (REGIN), IC2.8 (VBUS), X1.1
VHIGH: C4.1, D1.C, U$5.3 (IN), U$6.P$2 (+)
VIN: D1.A, J1.3
~CAS: IC1.86 (IO_37), U$26.16 (!CAS)
~CE: AS.6, IC1.21 (NCE), R31.1
~CONFIG: AS.5, IC1.14 (NCONFIG), R58.2
~CS: IC1.59 (IO_21), U$26.18 (!CS)
~CSO: AS.8, IC1.8 (IO_3), U$16.1 (~CS)
~RAS: IC1.85 (IO_36), U$26.17 (!RAS)

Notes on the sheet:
Bank 5 has 7 IO pins.
Bank 6 has 8 IO pins
Bank 7 has 10 IO pins
Bank 8 has 10 IO pins
Bank 1 has 6 IO pins
Bank 2 has 5 IO pins
Bank 3 has 8 IO pins
Bank 4 has 12 IO pins

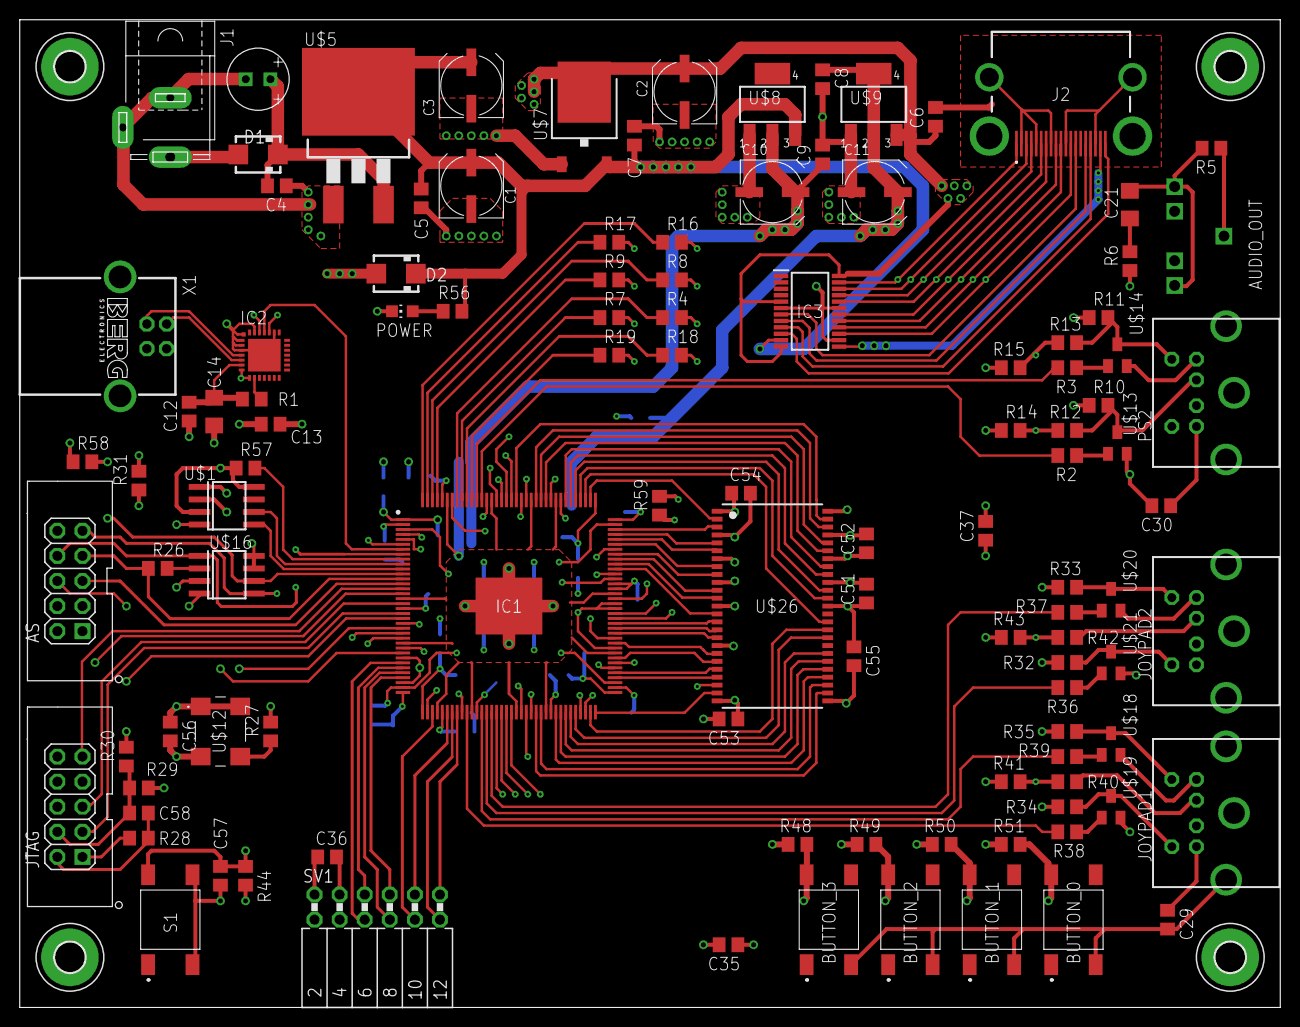
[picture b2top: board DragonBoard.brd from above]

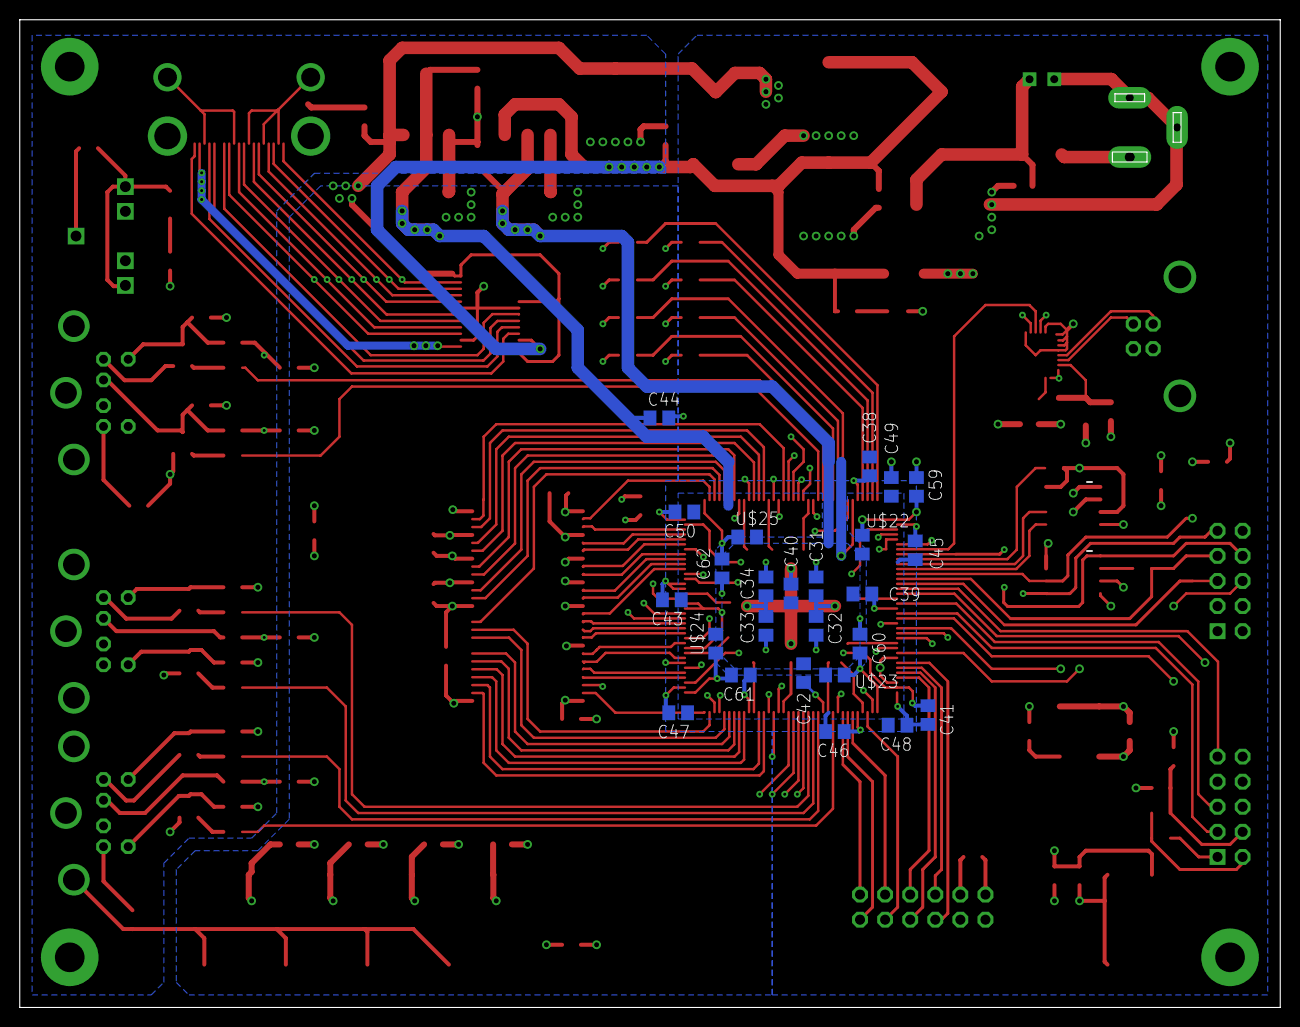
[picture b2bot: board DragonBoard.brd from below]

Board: 4 copper layers, 127.6 x 100.0 mm, 139 parts (25 on the bottom side), 136 nets.

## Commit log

2021-05-07 Added Eagle files
2021-08-12 new revisions
2021-09-26 Added eagle library file
2024-01-03 Added revision 2.0
2024-02-11 created BOM for rev 2.0
2025-04-16 fixed HDMI signal names in V2.0, fixed missing I2C resistors in V1.0
